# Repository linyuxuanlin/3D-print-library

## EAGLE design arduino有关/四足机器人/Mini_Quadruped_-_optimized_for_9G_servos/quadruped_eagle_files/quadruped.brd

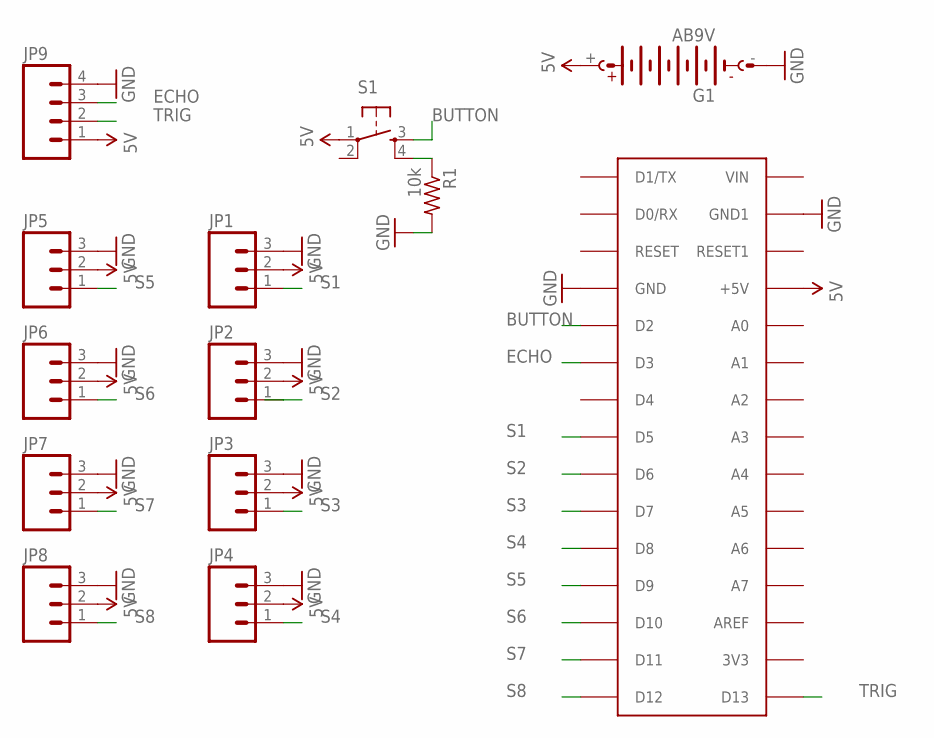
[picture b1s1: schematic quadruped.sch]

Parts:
G1: AB9V
JP1, JP2, JP3, JP4, JP5, JP6, JP7, JP8: M03PTH; 1X03
JP9: M04PTH; 1X04
R1: 10k; 0204/7
S1: TAC_SWITCHPTH; TACTILE-PTH
U$1: ARDUINONANO; PDIP-32

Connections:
5V: G1.+, JP1.2, JP2.2, JP3.2, JP4.2, JP5.2, JP6.2, JP7.2, JP8.2, JP9.1, S1.1, U$1.+5V
BUTTON: S1.3, U$1.D2
ECHO: JP9.3, U$1.D3
GND: G1.-, JP1.3, JP2.3, JP3.3, JP4.3, JP5.3, JP6.3, JP7.3, JP8.3, JP9.4, R1.2, U$1.GND, U$1.GND1
unnamed: R1.1, S1.4
S1: JP1.1, U$1.D5
S2: JP2.1, U$1.D6
S3: JP3.1, U$1.D7
S4: JP4.1, U$1.D8
S5: JP5.1, U$1.D9
S6: JP6.1, U$1.D10
S7: JP7.1, U$1.D11
S8: JP8.1, U$1.D12
TRIG: JP9.2, U$1.D13

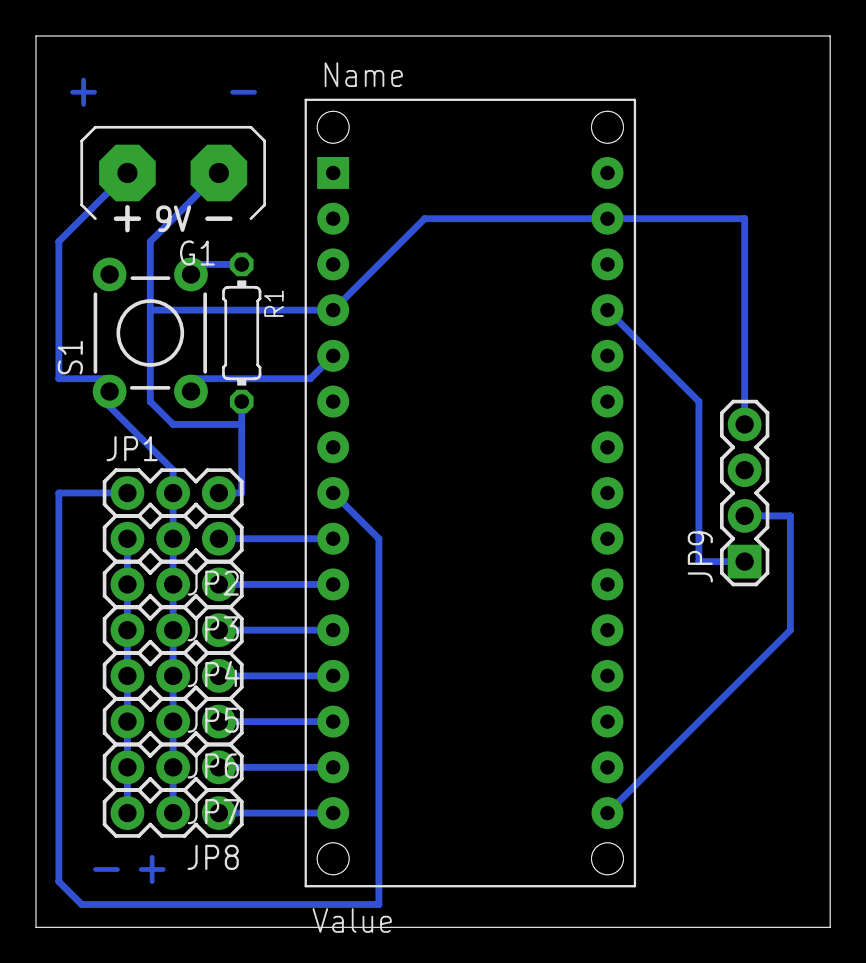
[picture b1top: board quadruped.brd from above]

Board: 2 copper layers, 44.1 x 49.5 mm, 13 parts (0 on the bottom side), 14 nets.

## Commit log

2017-05-13 1
    1
2021-02-18 Rename arduino有关/Cartesio/Death_to_Sharpie2/GCODE\14.GCODE to arduino 有关/Cartesio/Death_to_Sharpie2/GCODE14.GCODE

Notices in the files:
parts and their libraries:
SparkFun: Licensing: CC v3.0 Share-Alike You are welcome to use this library for commercial purposes.
